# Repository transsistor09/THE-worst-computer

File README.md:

<!DOCTYPE html>
<html>
<head>
  <meta charset="utf-8">
  <title>THE-worst-computer</title>
  <style>
    body {
      font-family: monospace;
      background: #111;
      color: #eee;
      max-width: 900px;
      margin: auto;
      padding: 20px;
    }
    h1, h2 {
      margin-top: 30px;
    }
    hr {
      border: none;
      border-top: 1px solid #444;
      margin: 30px 0;
    }
    img {
      max-width: 100%;
      margin: 15px 0;
    }
  </style>
</head>

<body>

<h1>THE-worst-computer</h1>
<p>a shitty z80 computer</p>

<hr>

<h2>how to use :</h2>
<p>
1.download<br>
2.load the folder to kicad<br>
3.very good very nice
</p>

<hr>

<h2>preview :</h2>

<hr>

<hr>

<h2>why should you make this computer ?</h2>
<p>=idk</p>

<h2>why did i make the "design" of this computer ?</h2>
<p>=bored</p>

<h2>am i going to get enough sleep ?</h2>
<p>=no</p>

<h2>did i actually make this ?</h2>
<p>=sadly yes</p>

<h2>is it done (fully) ?</h2>
<p>
=no and that is why i made a github page bc i cant make computers<br>
but hope fully thare are people more experienced than me
</p>

</body>
</html>

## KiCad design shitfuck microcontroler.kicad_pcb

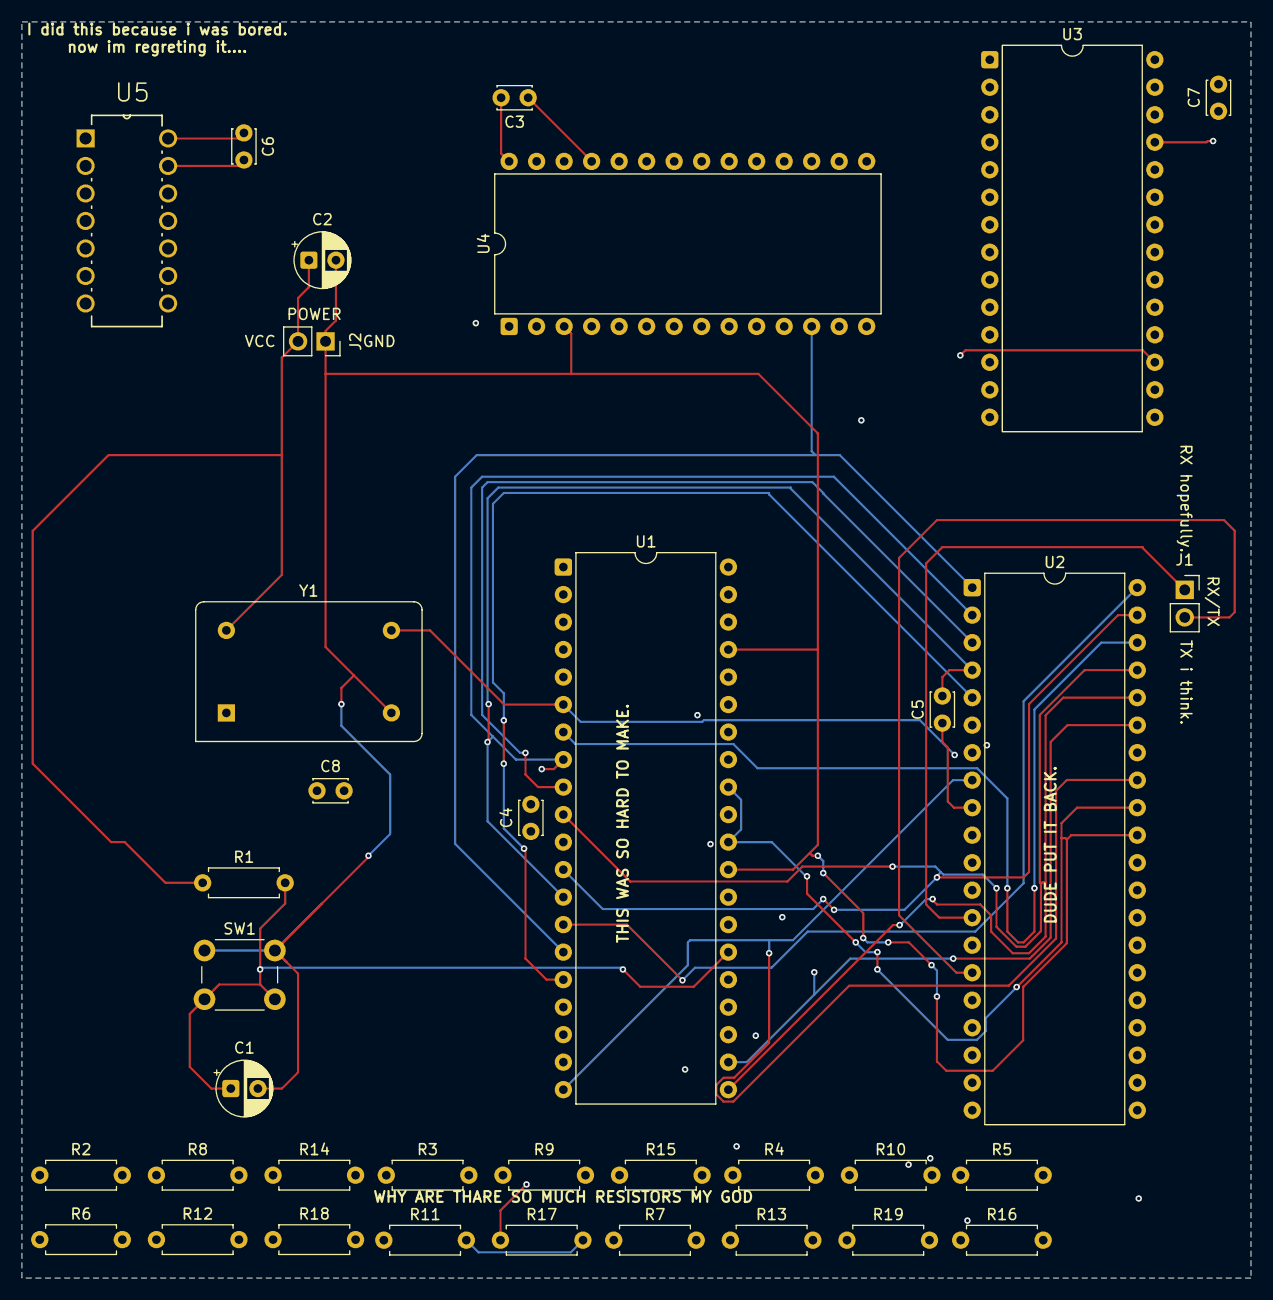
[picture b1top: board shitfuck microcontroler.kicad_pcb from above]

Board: 4 copper layers, 113.5 x 116.0 mm, 36 parts (0 on the bottom side), 33 nets.

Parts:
C1: C_Polarized,10µF; CP_Radial_D5.0mm_P2.50mm
C2: C_Polarized,22µF; CP_Radial_D5.0mm_P2.50mm
C3, C4, C5, C6, C7, C8: C_0.1µF; C_Disc_D3.0mm_W2.0mm_P2.50mm
J1, J2: Conn_01x02_Pin; PinSocket_1x02_P2.54mm_Vertical
R1, R2, R3, R4, R5, R6, R7, R8, R9, R10, R11, R12, R13, R14, R15, R16, R17, R18, R19: 10k; R_Axial_DIN0207_L6.3mm_D2.5mm_P7.62mm_Horizontal
SW1: SW_Push; SW_PUSH_6mm
U1: Z84C0020PEC; DIP-40_W15.24mm
U2: Z8530; DIP-40_W15.24mm
U3: KM62256CLP; DIP-28_W15.24mm
U4: 27C256; DIP-28_W15.24mm
U5: 74HC04N_652; DIP254P762X420-14
Y1: GTXO-14T 4MHZ; Oscillator_DIP-14

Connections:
/GND: C1.2, C2.2, C3.1, C4.2, C5.2, C6.2, C7.1, C8.2, J2.1, SW1.1, U1.1 (A_{11}), U1.8 (D_{3}), U1.13 (D_{7}), U1.29 (GND), U1.30 (A_{0}), U1.32 (A_{2}), U1.33 (A_{3}), U1.37 (A_{7}), U1.38 (A_{8}), U2.2 (D3), U2.4 (D7), U2.31 (GND), U2.32 (D/~C), U3.3 (A7), U3.7 (A3), U3.8 (A2), U3.10 (A0), U3.14 (GND), U3.15 (Q3), U3.19 (Q7), U3.23 (A11), U3.25 (A8), U4.3 (A7), U4.7 (A3), U4.8 (A2), U4.10 (A0), U4.14 (GND), U4.15 (D3), U4.19 (D7), U4.23 (A11), U4.25 (A8), U5.3 (2A), U5.5 (3A), U5.7 (GND), U5.9 (4A), U5.11 (5A), U5.13 (6A), Y1.7 (GND)
unnamed: J1.1, U2.13 (RXDA)
unnamed: J1.2, U2.15 (TXDA)
unnamed: C2.1, C3.2, C4.1, C5.1, C6.1, C7.2, C8.1, J2.2, R1.1, R7.1, R8.1, R9.2, R10.2, R11.2, R12.2, R13.2, R14.2, R15.2, R16.2, R17.2, R18.2, R19.2, U1.11 (V_{CC}), U2.9 (VCC), U3.28 (VCC), U4.1 (VPP), U4.28 (VCC), U5.14 (VCC), Y1.14 (Vcc)
unnamed: U1.31 (A_{1}), U3.9 (A1), U4.9 (A1)
unnamed: R10.1, U1.22 (~WR), U1.34 (A_{4}), U2.35 (~WR), U3.6 (A4), U4.6 (A4)
unnamed: U1.14 (D_{0}), U1.35 (A_{5}), U2.40 (D0), U3.5 (A5), U3.11 (Q0), U4.5 (A5), U4.11 (D0)
unnamed: U1.9 (D_{5}), U1.36 (A_{6}), U2.3 (D5), U3.4 (A6), U3.17 (Q5), U4.4 (A6), U4.17 (D5)
unnamed: U1.39 (A_{9}), U4.24 (A9)
unnamed: R9.1, U1.2 (A_{12}), U1.3 (A_{13}), U1.5 (A_{15}), U1.10 (D_{6}), U1.12 (D_{2}), U1.19 (~MREQ), U1.21 (~RD), U1.40 (A_{10}), U2.36 (~RD), U2.37 (D6), U2.39 (D2), U3.2 (A12), U3.13 (Q2), U3.18 (Q6), U3.20 (~CS), U3.21 (A10), U3.22 (~OE), U3.24 (A9), U3.26 (A13), U3.27 (~WE), U4.2 (A12), U4.13 (D2), U4.18 (D6), U4.20 (~CE), U4.21 (A10), U4.22 (~OE), U4.26 (A13), U5.1 (1A), U5.2 (1Y)
unnamed: U1.4 (A_{14}), U3.1 (A14), U4.27 (A14)
unnamed: U1.6 (CLK), U2.12 (~RTXCA), U2.14 (~TRXCA), U2.20 (PCLK), Y1.8 (OUT)
unnamed: U1.15 (D_{1}), U2.1 (D1), U3.12 (Q1), U4.12 (D1)
unnamed: U1.7 (D_{4}), U2.38 (D4), U3.16 (Q4), U4.16 (D4)
unnamed: R6.2, U1.23 (~BUSACK)
unnamed: R5.2, U1.25 (~BUSREQ)
unnamed: R3.2, U1.18 (~HALT)
unnamed: U1.16 (~INT), U2.5 (~INT)
unnamed: U1.20 (~IORQ), U2.8 (~INTACK), U2.33 (~CE)
unnamed: R4.2, U1.17 (~NMI)
unnamed: C1.1, R1.2, R2.1, R3.1, R4.1, R5.1, R6.1, SW1.2, U1.26 (~RESET)
unnamed: R2.2, U1.24 (~WAIT)
unnamed: R8.2, U2.7 (IEI)
unnamed: R7.2, U2.6 (IEO)
unnamed: R17.1, U2.18 (~CTSA)
unnamed: R15.1, U2.22 (~CTSB)
unnamed: R16.1, U2.21 (~DCDB)
unnamed: R18.1, U2.16 (~DTR/REQA)
unnamed: R14.1, U2.24 (~DTR/REQB)
unnamed: R11.1, U2.11 (~SYNCA)
unnamed: R19.1, U2.29 (~SYNCB)
unnamed: R12.1, U2.10 (~W/REQA)
unnamed: R13.1, U2.30 (~W/REQB)

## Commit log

2025-12-08 main
2026-06-23 Remove donation section from README
    Removed donation request and associated image from README.
